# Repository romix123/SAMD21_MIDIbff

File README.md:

# SAMD21_MIDIbff
 USB midi <-> TRS-b converter

I came across todbot's qtpy_midibff and thought I can share my attempt to design a USB <-> TRS-b converter as well, so here it is.

The board has the same footprint (and should be pin compatible) with the Wemos D1 mini board, making it a versatile little board. It comes with TRS-b midi in/out, a USB host port, a micro USB port for powering the board and a WS2812 (neopixel). The firmware is very rudimentary and not thoroughly tested.

Use at your own risk.

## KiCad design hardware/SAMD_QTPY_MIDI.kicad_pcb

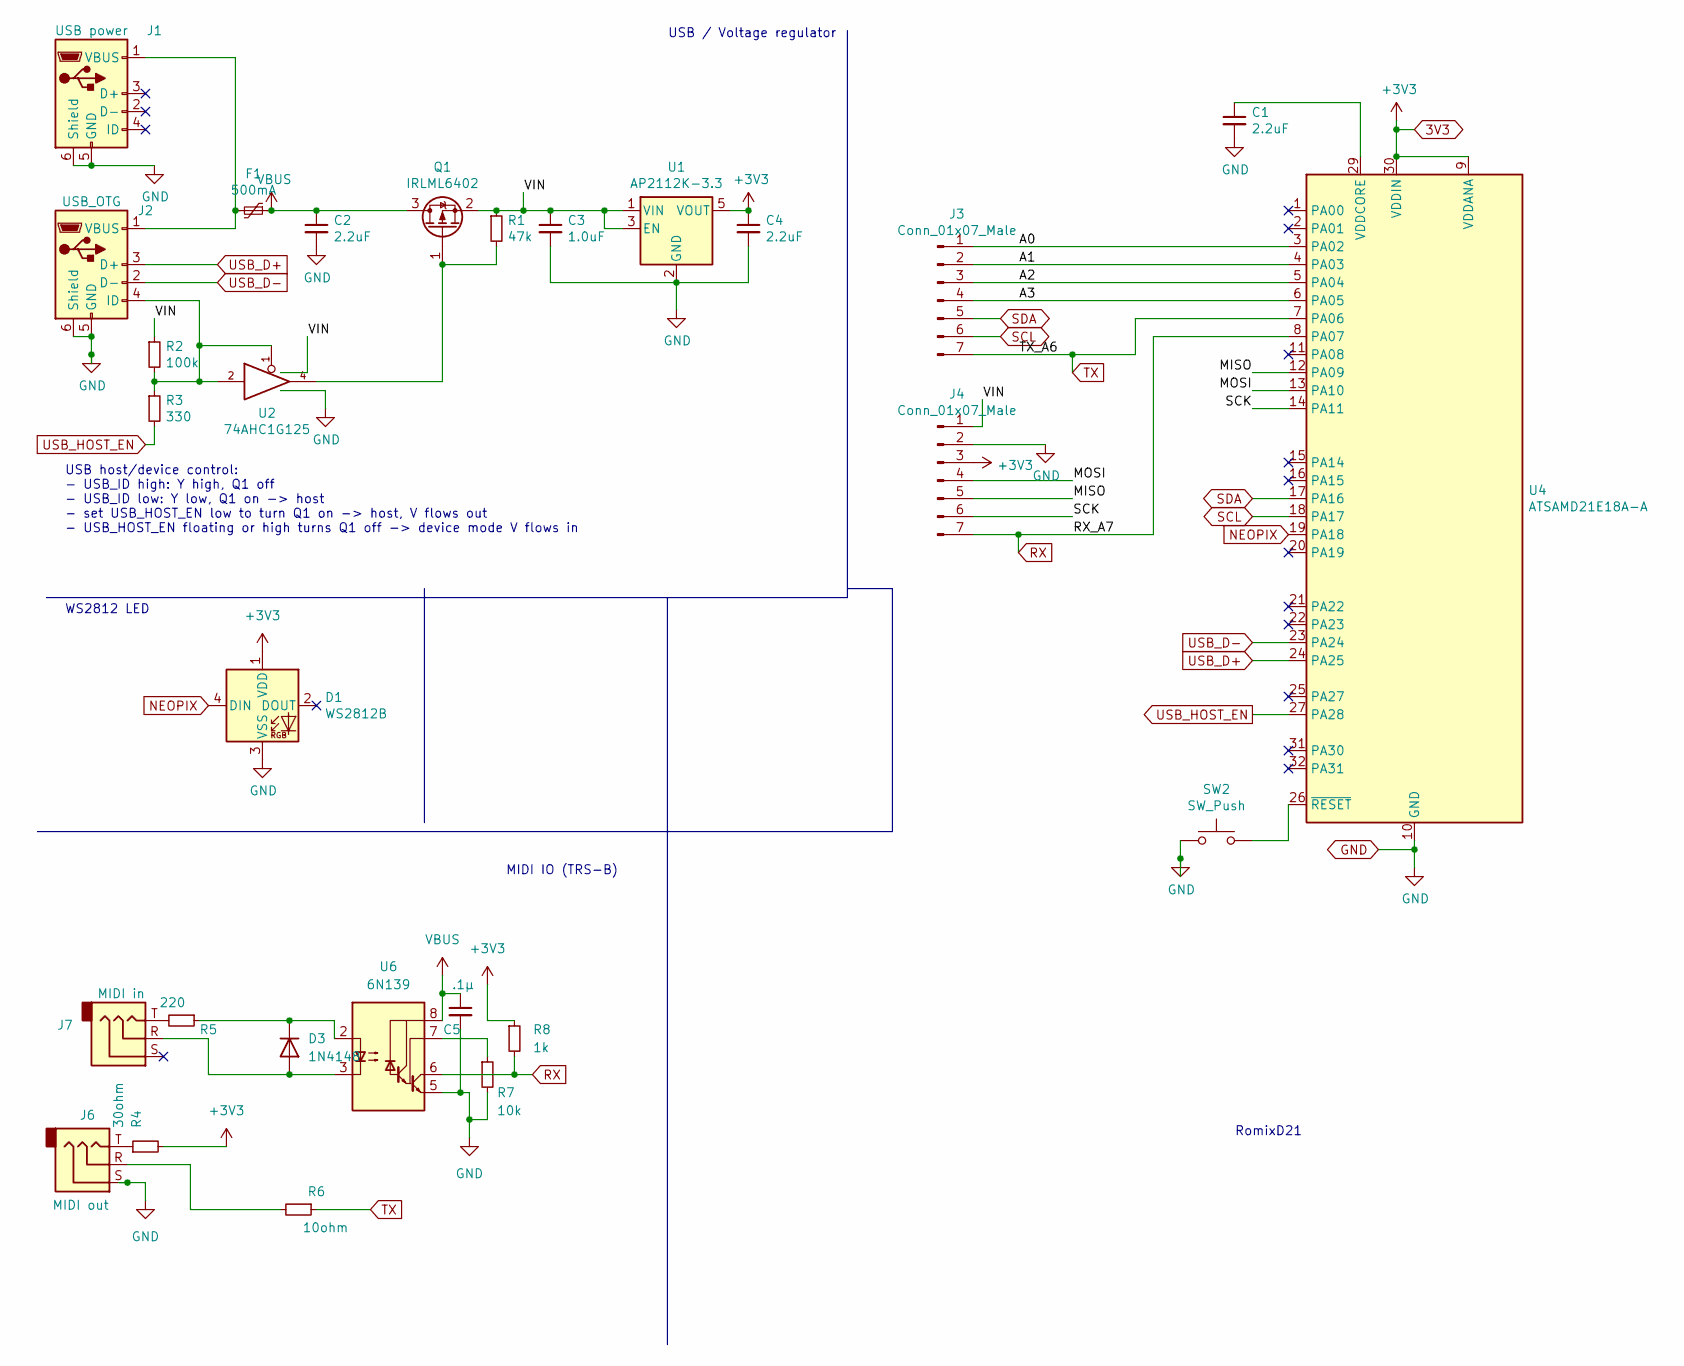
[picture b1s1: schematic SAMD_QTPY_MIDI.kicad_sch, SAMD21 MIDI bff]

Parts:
C1, C2, C4: 2.2uF; C_1206_3216Metric
C3: 1.0uF; C_1206_3216Metric
C5: .1µ; C_1206_3216Metric
D1: WS2812B; LED_WS2812B_PLCC4_5.0x5.0mm_P3.2mm
D3: 1N4148; D_SOD-123
F1: 500mA; Fuse_1206_3216Metric
J1: USB power; USB_Micro-B_Ali_power_only
J2: USB_OTG; USB_Micro-B_Amphenol_10104110_Horizontal
J3, J4: Conn_01x07_Male; PinHeader_1x07_P2.54mm_Vertical
J6: MIDI out; Jack_3.5mm_PJ313D_Horizontal
J7: MIDI in; Jack_3.5mm_PJ313D_Horizontal
Q1: IRLML6402; SOT-23
R1: 47k; R_1206_3216Metric
R2: 100k; R_1206_3216Metric
R3: 330; R_1206_3216Metric
R4: 30ohm; R_1206_3216Metric
R5: 220; R_1206_3216Metric
R6: 10ohm; R_1206_3216Metric
R7: 10k; R_1206_3216Metric
R8: 1k; R_1206_3216Metric
SW2: SW_Push; SW_SPST_EVQP7A
U1: AP2112K-3.3; SOT-23-5
U2: 74AHC1G125; SOT-23-5_HandSoldering
U4: ATSAMD21E18A-A; TQFP-32_7x7mm_P0.8mm
U6: 6N139; DIP-8_W7.62mm_SMDSocket_SmallPads

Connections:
3V3: C4.1, D1.1 (VDD), J4.3, R4.2, R8.1, U1.5 (VOUT), U4.9 (VDDANA), U4.30 (VDDIN)
/A0: J3.1, U4.3 (PA02)
/A1: J3.2, U4.4 (PA03)
/A2: J3.3, U4.5 (PA04)
/A3: J3.4, U4.6 (PA05)
/MISO: J4.5, U4.12 (PA09)
/MOSI: J4.4, U4.13 (PA10)
/SCK: J4.6, U4.14 (PA11)
GND: C1.2, C2.2, C3.2, C4.2, C5.2, D1.3 (VSS), J1.5 (GND), J1.6 (Shield), J2.5 (GND), J2.6 (Shield), J4.2, J6.S, R7.2, SW2.1, U1.2 (GND), U2.3 (GND), U4.10 (GND), U4.28 (GND), U6.5 (GND)
NEOPIX: D1.4 (DIN), U4.19 (PA18)
unnamed: C1.1, U4.29 (VDDCORE)
unnamed: D3.1 (K), R5.1, U6.2 (C1)
unnamed: D3.2 (A), J7.R, U6.3 (C2)
unnamed: F1.2, J1.1 (VBUS), J2.1 (VBUS)
unnamed: J6.T, R4.1
unnamed: J7.T, R5.2
unnamed: Q1.1 (G), R1.2, U2.4
unnamed: J2.4 (ID), R2.2, R3.1, U2.1, U2.2
unnamed: J6.R, R6.2
unnamed: R7.1, U6.7 (VO1)
unnamed: SW2.2, U4.26 (~RESET)
RX: J4.7, R8.2, U4.8 (PA07), U6.6 (VO2)
SCL: J3.6, U4.18 (PA17)
SDA: J3.5, U4.17 (PA16)
TX: J3.7, R6.1, U4.7 (PA06)
USB_D+: J2.3 (D+), U4.24 (PA25)
USB_D-: J2.2 (D-), U4.23 (PA24)
USB_HOST_EN: R3.2, U4.27 (PA28)
VBUS: C2.1, C5.1, F1.1, Q1.3 (D), U6.8 (VCC)
VCC: C3.1, J4.1, Q1.2 (S), R1.1, R2.1, U1.1 (VIN), U1.3 (EN), U2.5 (VCC)

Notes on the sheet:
WS2812 LED
USB host/device control: - USB_ID high: Y high, Q1 off - USB_ID low: Y low, Q1 on -> host - set USB_HOST_EN low to turn Q1 on -> host, V flows out - USB_HOST_EN floating or high turns Q1 off -> device mode V flows in
MIDI IO (TRS-B)
USB / Voltage regulator
RomixD21

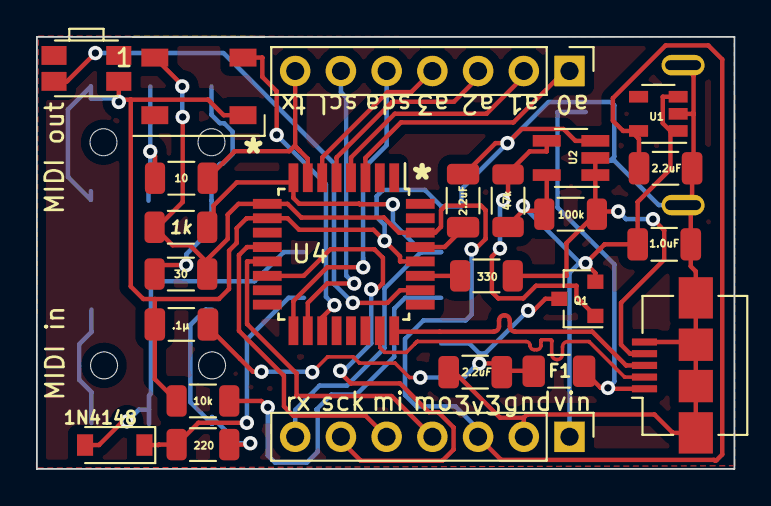
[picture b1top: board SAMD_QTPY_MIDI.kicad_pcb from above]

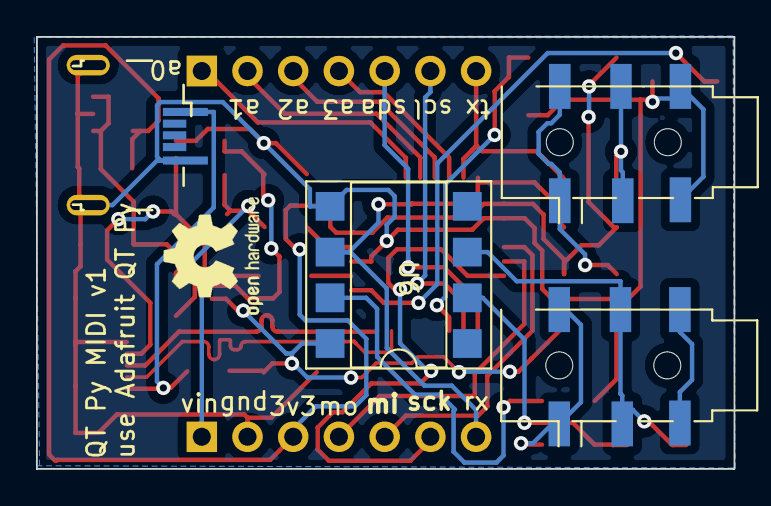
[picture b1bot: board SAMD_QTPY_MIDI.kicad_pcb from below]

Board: 2 copper layers, 38.8 x 24.0 mm, 28 parts (4 on the bottom side), 30 nets.

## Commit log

2022-08-13 fixed pics
